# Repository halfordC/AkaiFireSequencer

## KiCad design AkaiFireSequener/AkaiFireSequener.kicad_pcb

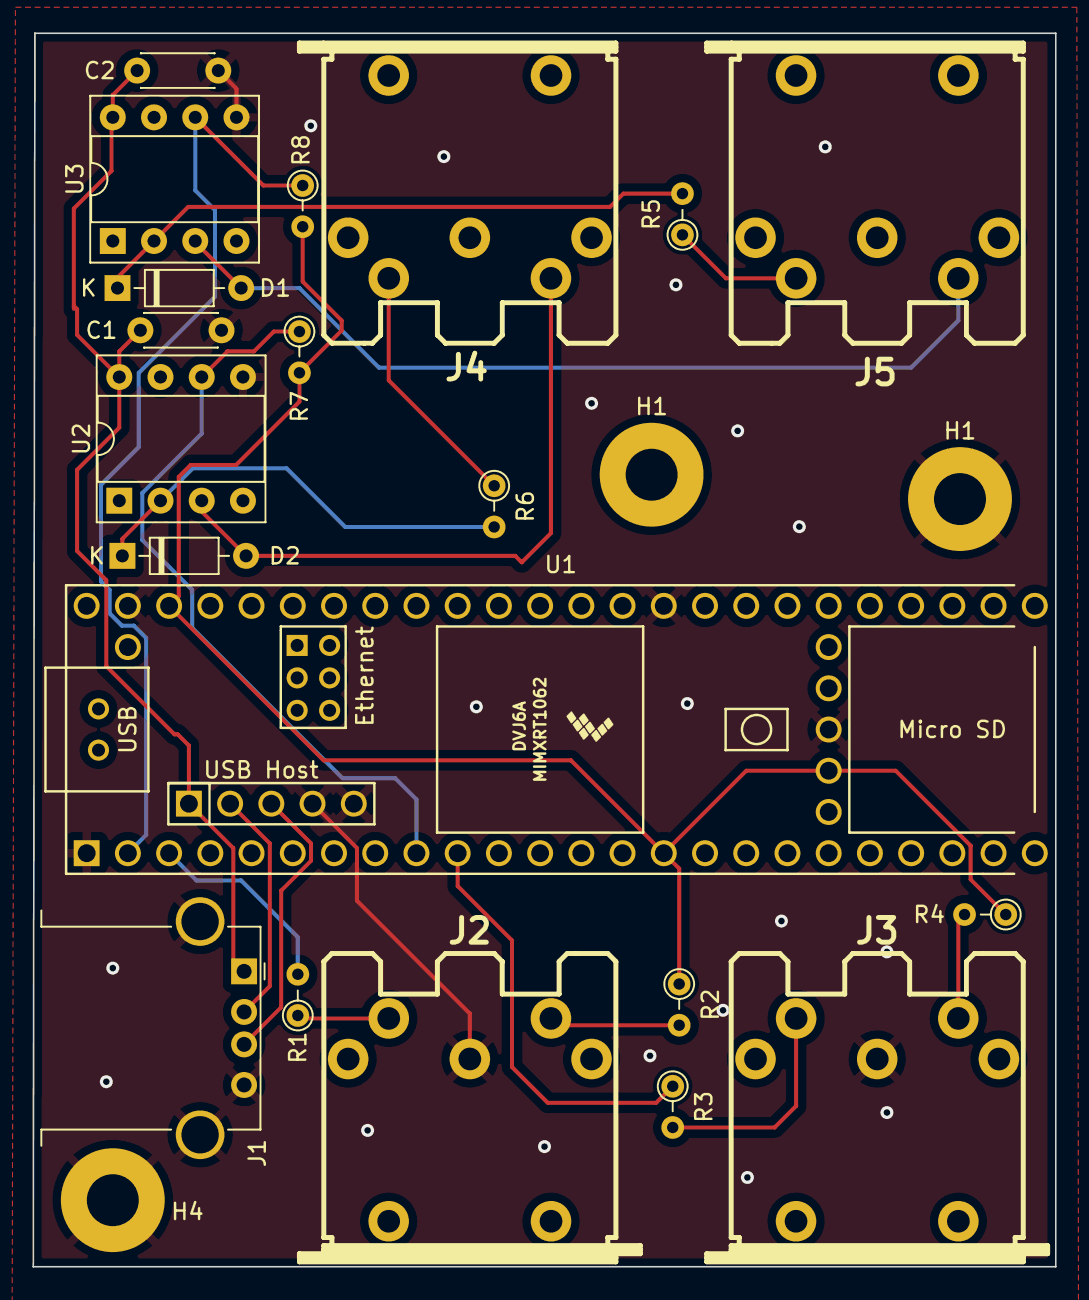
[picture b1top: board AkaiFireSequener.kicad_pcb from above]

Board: 2 copper layers, 63.0 x 76.0 mm, 23 parts (0 on the bottom side), 19 nets.

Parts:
C1, C2: 0.1uF; C_Disc_D4.3mm_W1.9mm_P5.00mm
D1, D2: 1N4148; D_DO-35_SOD27_P7.62mm_Horizontal
H1, H1#2, H4: MountingHole_Pad; MountingHole_3.2mm_M3_Pad
J1: USB_A; USB_A_Stewart_SS-52100-001_Horizontal
J2, J3, J4, J5: DIN-5_180degree; MIDI_DIN5
R1, R2, R3, R4: 47; R_Axial_DIN0204_L3.6mm_D1.6mm_P2.54mm_Vertical
R5, R6: 220; R_Axial_DIN0204_L3.6mm_D1.6mm_P2.54mm_Vertical
R7, R8: 470; R_Axial_DIN0204_L3.6mm_D1.6mm_P2.54mm_Vertical
U1: Teensy4.1; Teensy41
U2, U3: 6N138; DIP-8_W7.62mm_Socket

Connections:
+3.3V: R2.1, R4.1, R7.2, R8.2, U1.15 (3V3), U1.46 (3V3), U1.51 (3V3)
+5V: C1.1, C2.1, J1.1 (VBUS), U1.55 (5V), U2.8 (VCC), U3.8 (VCC)
GND: C1.2, C2.2, H1#2.1, H4.1, J1.4 (GND), J1.5 (Shield), J2.2, J3.2, U1.1 (GND), U1.34 (GND), U1.47 (GND), U1.52 (GND), U1.58 (GND), U1.59 (GND), U2.5 (GND), U3.5 (GND)
unnamed: D1.1 (K), R5.2, U3.2 (C1)
unnamed: D1.2 (A), J5.5, U3.3 (C2)
unnamed: D2.1 (K), R6.2, U2.2 (C1)
unnamed: D2.2 (A), J4.5, U2.3 (C2)
unnamed: J1.2 (D-), U1.56 (D-)
unnamed: J1.3 (D+), U1.57 (D+)
unnamed: J2.4, R2.2
unnamed: J2.5, R1.1
unnamed: J3.4, R4.2
unnamed: J3.5, R3.2
unnamed: J4.4, R6.1
unnamed: J5.4, R5.1
unnamed: R1.2, U1.3 (1_TX1_CTX2_MISO1)
unnamed: R8.1, U1.2 (0_RX1_CRX2_CS1), U3.6 (VO2)
unnamed: R7.1, U1.9 (7_RX2_OUT1A), U2.6 (VO2)
unnamed: R3.1, U1.10 (8_TX2_IN1)
